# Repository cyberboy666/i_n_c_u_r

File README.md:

# i_n_c_u_r

### a [r_e_c_u_r](https://github.com/cyberboy666/r_e_c_u_r) video sampler extension circuit - adding knobs, cv and serial midi control

- this circuit is distributed by __UNDERSCORES__ - _an open video hardware label_ : it is available to purchase - as a pcb, kit or assembled unit - at [underscores.shop](https://underscores.shop/i_n_c_u_r/)
- the schematic for the circuit can be found [here](/hardware/schematic.pdf)
- the pcb gerber files for the lastest version can be found [here](/hardware/gerber_latest.zip)
- interactive BOM is [here](https://htmlpreview.github.io/?https://github.com/cyberboy666/i_n_c_u_r/blob/main/hardware/bom/ibom.html)
- consider [donating](https://opencollective.com/underscores) to the underscores project to help us continue creating for the commons

## description

__NOTE__ : _i_n_c_u_r_ is an extension circuit for my existing raspberry pi project [r_e_c_u_r](https://github.com/cyberboy666/r_e_c_u_r) - it will only be useful to you if you already have build a r_e_c_u_r

_disclaimer: this is a fun custom project, but dont forget there are other ways to getting serial and cv control over recur parameters. USB midi is supported in recur without any extra circuitry. other [diy](https://aemodular.boards.net/thread/141/simple-cv-midi-converter-arduino) and [commercial](https://www.befaco.org/en/vcmc/) products exist that convert cv to midi, and serial to USB. in my opinion a general solution for cv-to-usb-midi applied to recur is more useful than a specific board that only works with recur_

- 4x __knobs__ for physical control over shader parameters
- 4x __cv jacks (0-5v)__ for sequenced control over shader parameters (from older/analog synths eg eurorack)
- __serial midi__ din5 jack for sequenced control over shader parameters (from older midi devices)
- exposes _rpi video output through rca jack_ (rather than the 3.5mm trrs jack on pi )
- mounting holes and front facing interface parts for easier racking / enclosure building
- interfacing with rpi through gpio leaving all usb jacks free

## demo videos

# documentation

this project is fully _open-source hardware_ - all the files required to build it are included in this repo for free. if you have the time and/or skill you can contribute back by collaborating on / testing new designs, improving these docs, making demo videos/other creative content etc. you can also support the project financially by [donating directing](https://opencollective.com/underscores), or purchasing through the [web shop](https://underscores.shop).

depending on whether you are going fully diy or buying an assembled and tested unit, some of the following guides will be relavent to you. the flow would be:

## ordering parts

<details><summary><b>parts sourcing guide (w/ notes on pcb fabracation )</b> - start here if you are building fully from scatch or have purchased a pcb</summary>

i try to source all the parts i can from either:
- [tayda](https://www.taydaelectronics.com/) ; cheaper for common parts like resistors etc, also good for mechanical parts like switches and buttons
- [mouser](https://www.mouser.de/) ; has lots more options, speciality video ic's, can sometimes cost more (free shipping on orders over 50euros)
- other ; ocationally there will be parts which will need to be sourced elsewhere - usaully either aliexpress, ebay or amazon etc...

take a look at the [full_bom](/hardware/bom/full_bom.csv) for this project to see where i am sourcing each part from

## import into tayda

- go to the [tayda quick order](https://www.taydaelectronics.com/quick-order/) and in bottom corner choose _add from file_
- select the file [tayda_bom.csv](./hardware/bom/tayda_bom.csv) in the BOM folder (you will have to download it first or clone this repo)
- after importing select _add to cart_
- __NOTE:__ the minimum value for resistors is 10, so you may need to modify these values to add to cart (or if they are already modified here you will need to see the  full_bom for actual part QTY) 

- OPTIONAL: it is a good idea to add some dip-ic sockets and 2.54pin headers/sockets to your tayda order if you dont have them around already
  
## import into mouser

- go to [mouser bom tool](https://nz.mouser.com/Bom/) and click _upload spreadsheet_
- select the file [mouser_bom.csv](./hardware/bom/mouser_bom.csv) in this folder (you will have to download it first or clone this repo), then _upload my spreadsheet_ and _next_
- ensure that __Mouser Part Number__ is selected in the dropdown above the first row, then _next_, _process_
- if everything looks correct can now put _add to basket_

# ordering pcbs

you can support this project by buying individual pcbs from the [shop](https://underscores.shop). if you would rather have pcbs fabricated from gerbers directly the file you need is [here](/hardware/gerber_latest.zip) 

- i get my pcbs fabricated from [jlcpcb](https://cart.jlcpcb.com/quote) - 5 is the minumum order per design
- upload the zip file with the `add gerber file` button
- the default settings are mostly fine - set the __PCB Qty__ and __PCB Color__ settings (you can check that the file looks correct with pcb veiwer)
- it may be best to combine orders with other pcbs you want to have fab'd since the shipping can cost more than the items - also orginising group buys is a good way to distribute the extra pcbs /costs 
  
i often use jlcpcb because they are reliable, cheap and give you an option of colours. remember though that the cheapest Chinese fab houses are not always the most ethical or environmently friendly - if you can afford it consider supporting local companies. 

</details>

## assembly guide

<details><summary><b>assembly guide</b> - start here if you have purchased a diy kit</summary>

## interactive BOM for build guiding

follow this link to view the [interactive BOM](https://htmlpreview.github.io/?https://github.com/cyberboy666/i_n_c_u_r/blob/main/hardware/bom/ibom.html)

## general solder advices

- remember to heat pad first (2-3seconds), then add solder, then continue to heat (1-2seconds)

- Checkout the web-comic [soldering is easy](https://mightyohm.com/files/soldercomic/FullSolderComic_EN.pdf) for more soldering advice

## general order of assembly

- in general while assembling i start placing resistors and capacitors first. placing 5 - 10 components at a time and then flipping the board to solder them and trim the legs etc.
- next i would do diodes, transistors and ic's - taking care that these are placed in the right direction (using a ic socket can be useful)
- finally i place the interface parts - rca jacks, power jack, pots and switches - make sure these have lots of solder on for structural stablity

## slightly more specific assembly advice

start with the lowest to place components : resistors, diodes, ic's

next i would place the two headers since soldering from the top can be awkward with too many components - __NOTE these need to be placed upside down!__ ,:

- J8 needs the pins facing up from top of pcb so the screen can go ontop and raspberry pi can go underneath
- J6 also needs to soldered from the top so a jumper from the pi board can be run to bottom of circuit

finally place the pots and jacks.
  
### rca video-out

if you want RCA video out from the pi on this pcb a jumper needs to be run from J6 to the composite video out on the raspberry pi board. on pi0 this is a labeled pin, however on pi3 you will need to solder directly to the board. i used a header-cable, cut one side to be soldered. The pin on pi3 is marked as PP24.

 [picture coming soon]
  
</details>
  
## operating guide
  
<details><summary><b>operating guide</b> - start here if you have purchased an assembled unit</summary>

- to enable the analog inputs ( knobs & cv ) go to `user_input` folder in r_e_c_u_r's `_SETTINGS_` tab and toggle `ANALOG_INPUT`
- to enable serial midi input go to `user_input` folder in r_e_c_u_r's `_SETTINGS_` tab and toggle `MIDI_INPUT` to _serial_
  
for more info on operating r_e_c_u_r see this [guide](https://github.com/cyberboy666/r_e_c_u_r/wiki/operate_docs)

</details>

### more info

<details><summary><b>how the circuit works</b></summary>

</details>

<details><summary><b>contributing guide</b></summary>
  
if you would like to contribute back to these projects in some way but dont know how the best thing (for now) would be to reach out to me directly ( tim@cyberboy666.com or @cyberboy666 on scanlines forum) - i will be happy to help
  
</details>

## community contributed enclosure designs:

- an [eurorack panel design](enclosure/i_n_c_u_r%20_%20eurorack_panel.stl) by [Simon Gorzelnik](https://www.instagram.com/shimon.jpg/)
- a [base enclosure](enclosure/INCUR%20enclosure%20base.stl) by [miles](mailto:milesjohnsonwashere@gmail.com)

## credits & more info

This circuit is distributed through UNDERSCORES – open video hardware label – visit [underscores.shop](https://underscores.shop) for more info

The pcb was designed using KICAD

Everything from gerbers, cad files, panels and documentation is freely available online and distributed under CC-BY-SA / open-source licenses – help us contribute to the commons !

Ask any questions or start discussions related to this project on the [scanlines.xyz](https://scanlines.xyz) forum – an online community space dedicated to diy av / electronic media art

You can contact me directly at tim (at) cyberboy666 (dot) com 
Please get in touch if you are interested in hosting a workshop !

Thanks to Signal Culture for giving me the time and space to explore. to Bastien Lavaud for circuit advice, always. To Ben Caldwell for project advice. To everyone who has or will contribute ♥♥♥

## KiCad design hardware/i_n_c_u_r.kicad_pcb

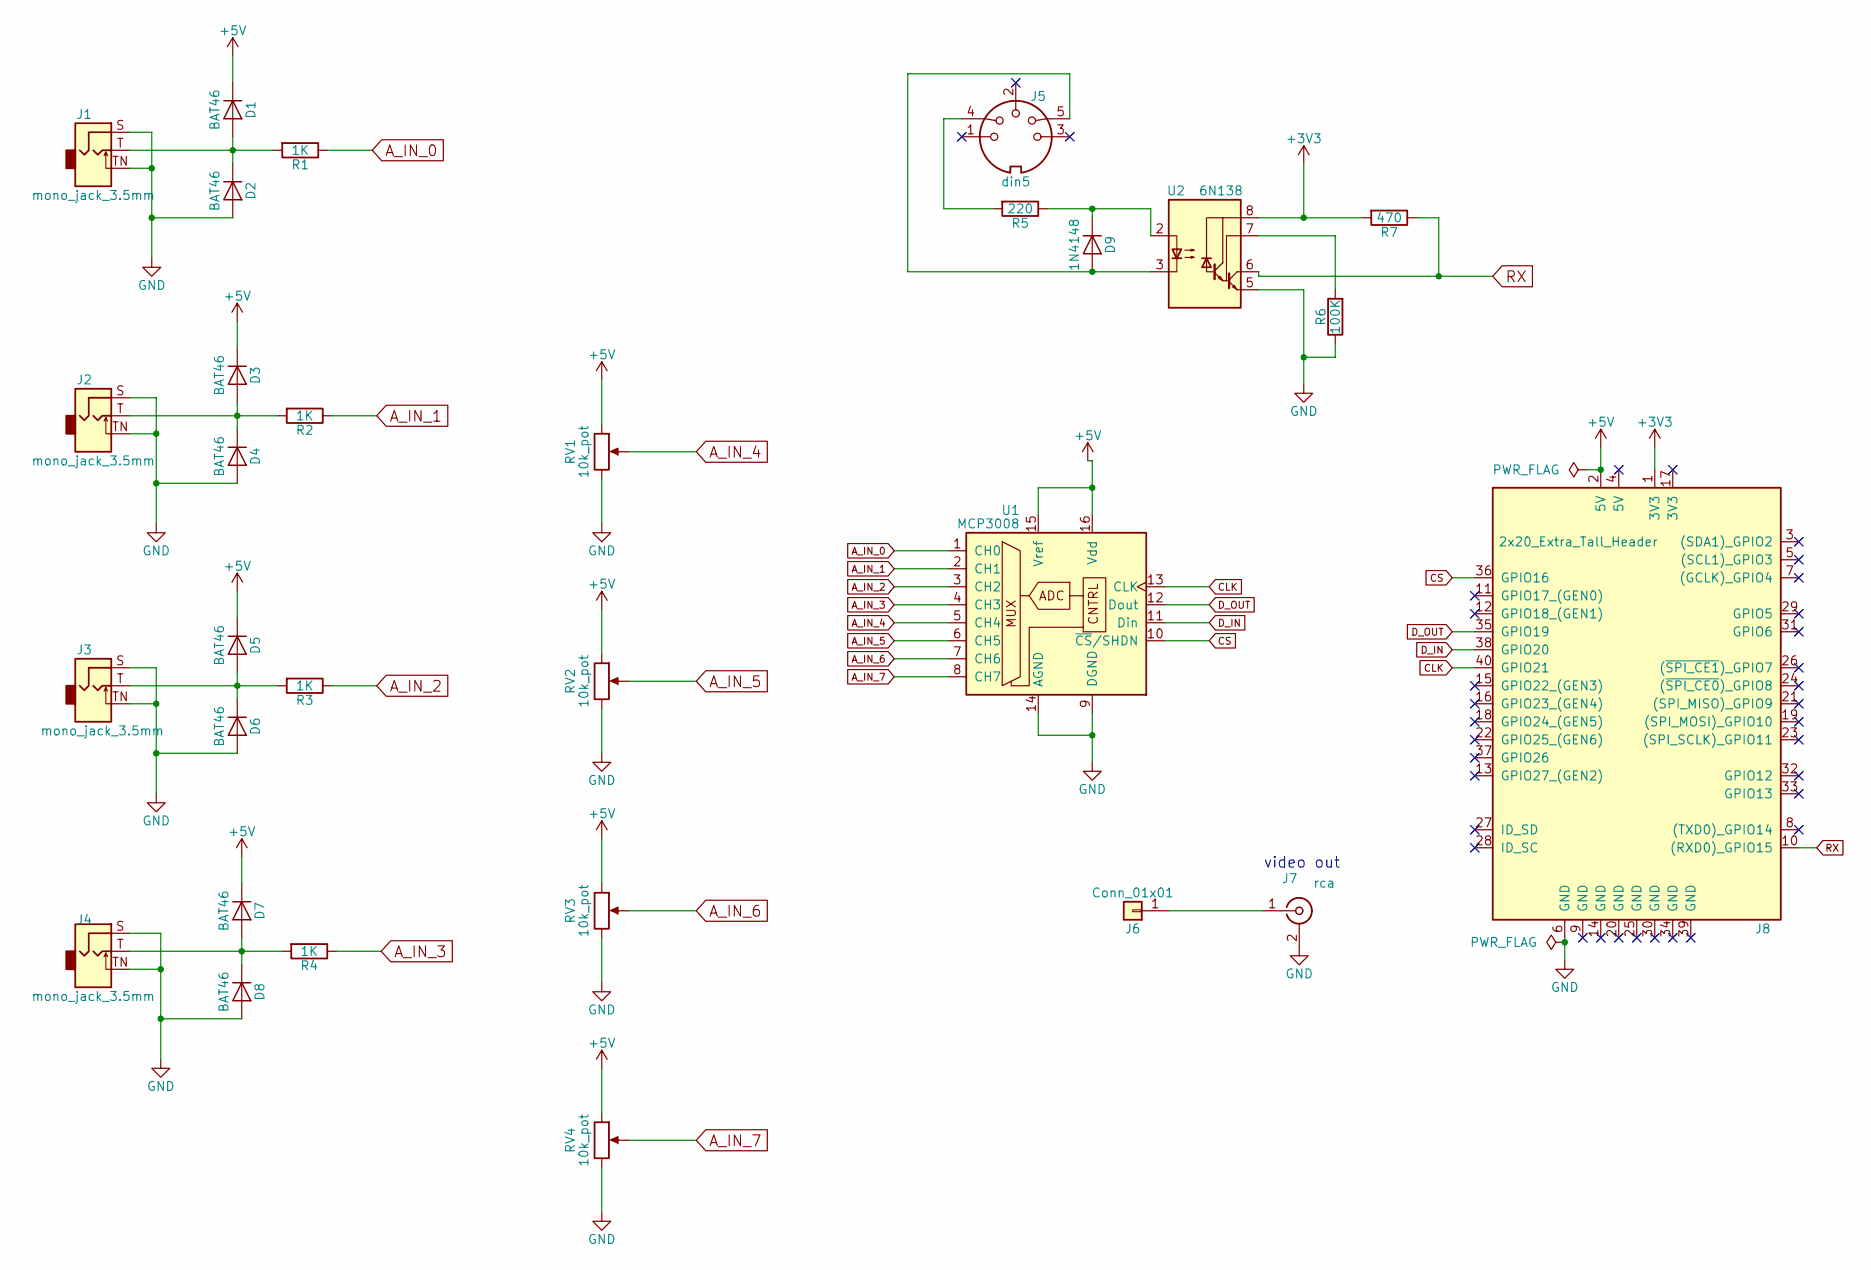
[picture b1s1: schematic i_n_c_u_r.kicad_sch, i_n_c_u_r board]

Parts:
D1, D2, D3, D4, D5, D6, D7, D8: BAT46; D_DO-35_SOD27_P5.08mm_Vertical_KathodeUp
D9: 1N4148; D_DO-35_SOD27_P5.08mm_Vertical_KathodeUp
J1, J2, J3, J4: mono_jack_3.5mm; Jack_3.5mm_QingPu_WQP-PJ398SM_Vertical_CircularHoles
J5: din5; tht_vertical_din5
J6: Conn_01x01; Pin_Header_Straight_1x01_Pitch2.54mm
J7: rca; tht_rca_vertical
J8: 2x20_Extra_Tall_Header; PinHeader_2x20_P2.54mm_Vertical
R1, R2, R3, R4: 1K; R_Axial_DIN0207_L6.3mm_D2.5mm_P7.62mm_Horizontal
R5: 220; R_Axial_DIN0207_L6.3mm_D2.5mm_P7.62mm_Horizontal
R6: 100K; R_Axial_DIN0207_L6.3mm_D2.5mm_P7.62mm_Horizontal
R7: 470; R_Axial_DIN0207_L6.3mm_D2.5mm_P7.62mm_Horizontal
RV1, RV2, RV3, RV4: 10k_pot; tht_vertical_potentiometer
U1: MCP3008; DIP-16_W7.62mm_LongPads
U2: 6N138; DIP-8_W7.62mm_LongPads

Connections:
+3V3: J8.1 (3V3), R7.2, U2.8 (VCC)
+5V: D1.1 (K), D3.1 (K), D5.1 (K), D7.1 (K), J8.2 (5V), RV1.1, RV2.1, RV3.1, RV4.1, U1.15 (Vref), U1.16 (Vdd)
A_IN_0: R1.1, U1.1 (CH0)
A_IN_1: R2.1, U1.2 (CH1)
A_IN_2: R3.1, U1.3 (CH2)
A_IN_3: R4.1, U1.4 (CH3)
A_IN_4: RV1.2, U1.5 (CH4)
A_IN_5: RV2.2, U1.6 (CH5)
A_IN_6: RV3.2, U1.7 (CH6)
A_IN_7: RV4.2, U1.8 (CH7)
CLK: J8.40 (GPIO21), U1.13 (CLK)
CS: J8.36 (GPIO16), U1.10 (~CS/SHDN)
D_IN: J8.38 (GPIO20), U1.11 (Din)
D_OUT: J8.35 (GPIO19), U1.12 (Dout)
GND: D2.2 (A), D4.2 (A), D6.2 (A), D8.2 (A), J1.S, J1.TN, J2.S, J2.TN, J3.S, J3.TN, J4.S, J4.TN, J7.2 (Ext), J8.6 (GND), R6.1, RV1.3, RV2.3, RV3.3, RV4.3, U1.9 (DGND), U1.14 (AGND), U2.5 (GND)
unnamed: D1.2 (A), D2.1 (K), J1.T, R1.2
unnamed: D3.2 (A), D4.1 (K), J2.T, R2.2
unnamed: D7.2 (A), D8.1 (K), J4.T, R4.2
unnamed: D9.1 (K), R5.1, U2.2 (C1)
unnamed: D9.2 (A), J5.5, U2.3 (C2)
unnamed: D5.2 (A), D6.1 (K), J3.T, R3.2
unnamed: J5.4, R5.2
unnamed: J6.1, J7.1 (In)
unnamed: R6.2, U2.7 (VO1)
RX: J8.10 ((RXD0)_GPIO15), R7.1, U2.6 (VO2)

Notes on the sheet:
video out

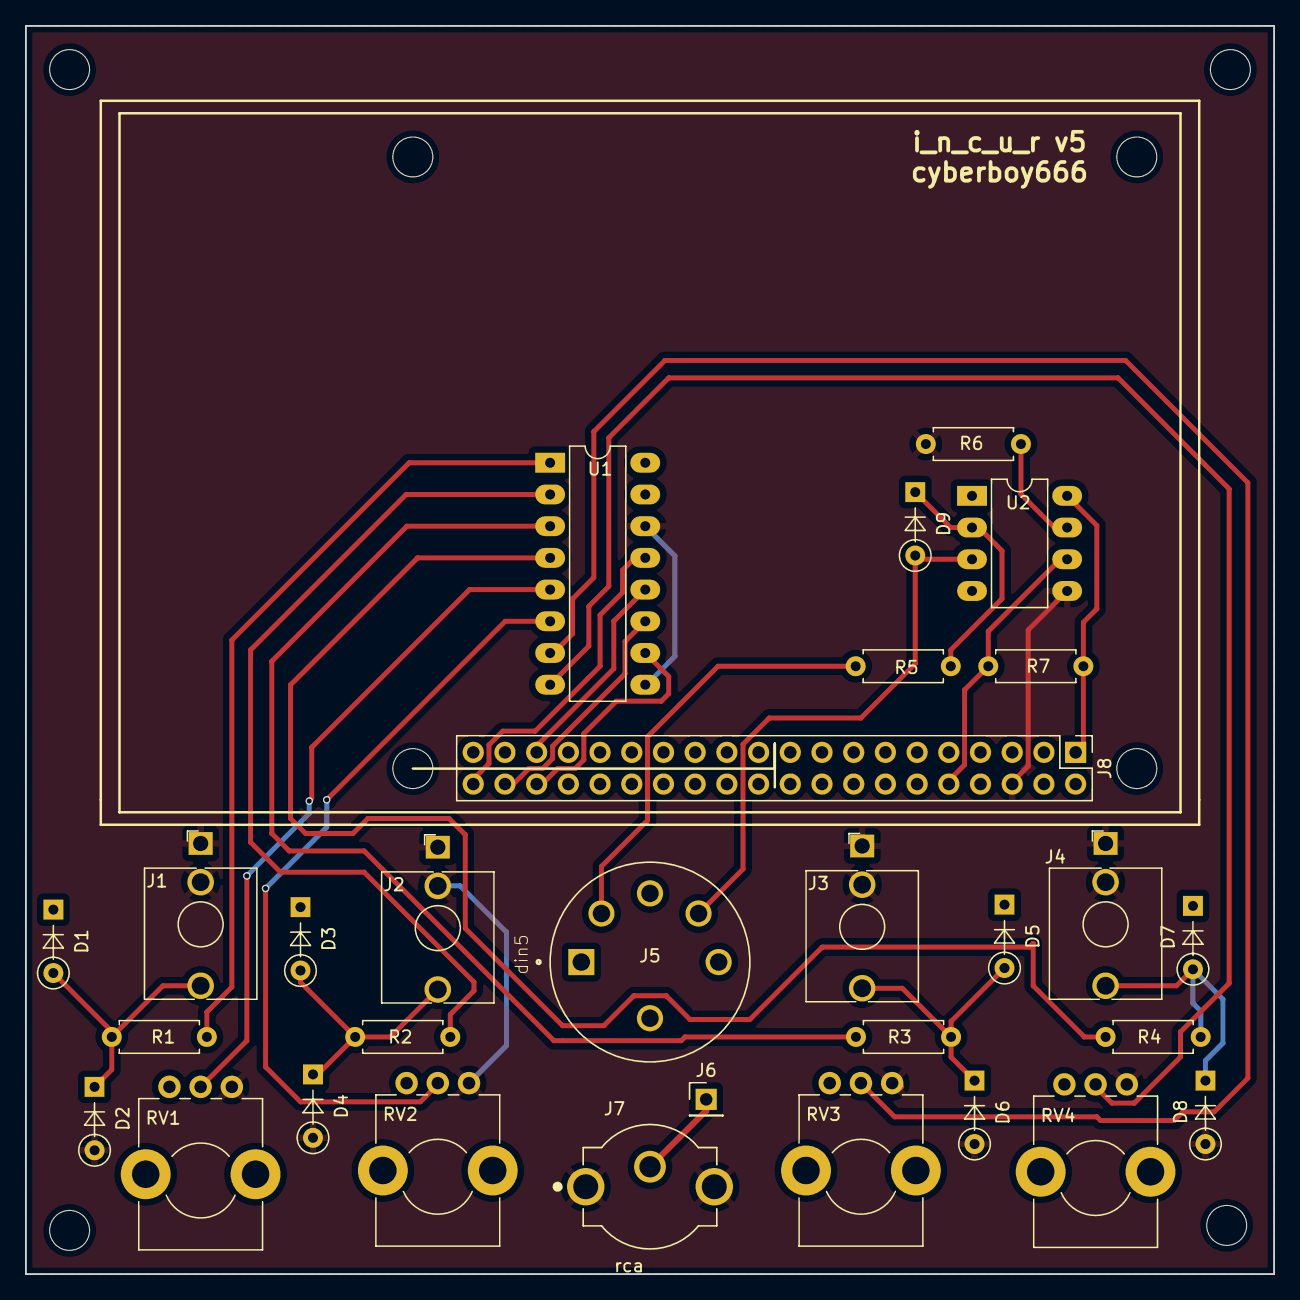
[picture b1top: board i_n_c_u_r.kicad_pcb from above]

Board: 2 copper layers, 100.0 x 100.0 mm, 30 parts (0 on the bottom side), 25 nets.

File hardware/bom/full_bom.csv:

sku,qty,ref,val,vendor
A-1095,8,D1 D2 D3 D4 D5 D6 D7 D8 ,BAT46,tayda
A-157,1,D9 ,1N4148,tayda
A-2563,4,J1 J2 J3 J4 ,mono_jack_3.5mm,tayda
490-SD-50BV,1,J5 ,din5,mouser
-,1,J6 ,Conn_01x01
490-RCJ-024,1,J7 ,rca,mouser
485-1979,1,J8 ,2x20_Extra_Tall_Header,mouser
A-2200,4,R1 R2 R3 R4 ,1K,tayda
A-2246,1,R5 ,220,tayda
A-2248,1,R6 ,100K,tayda
A-2247,1,R7 ,470,tayda
A-5531,4,RV1 RV2 RV3 RV4 ,10k_pot,tayda
A-2470,1,U1 ,MCP3008,tayda
859-6N138,1,U2 ,6N138,mouser

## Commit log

2022-01-11 migrate to own repo
2022-02-10 plot schematic
2022-02-22 renaming schematic
2022-02-22 rename kicad board
2022-02-28 update bom
2022-10-27 made pot holes bigger - small updates for kicad6
2023-07-12 add panel stuff
2024-05-19 add .gitattributes
